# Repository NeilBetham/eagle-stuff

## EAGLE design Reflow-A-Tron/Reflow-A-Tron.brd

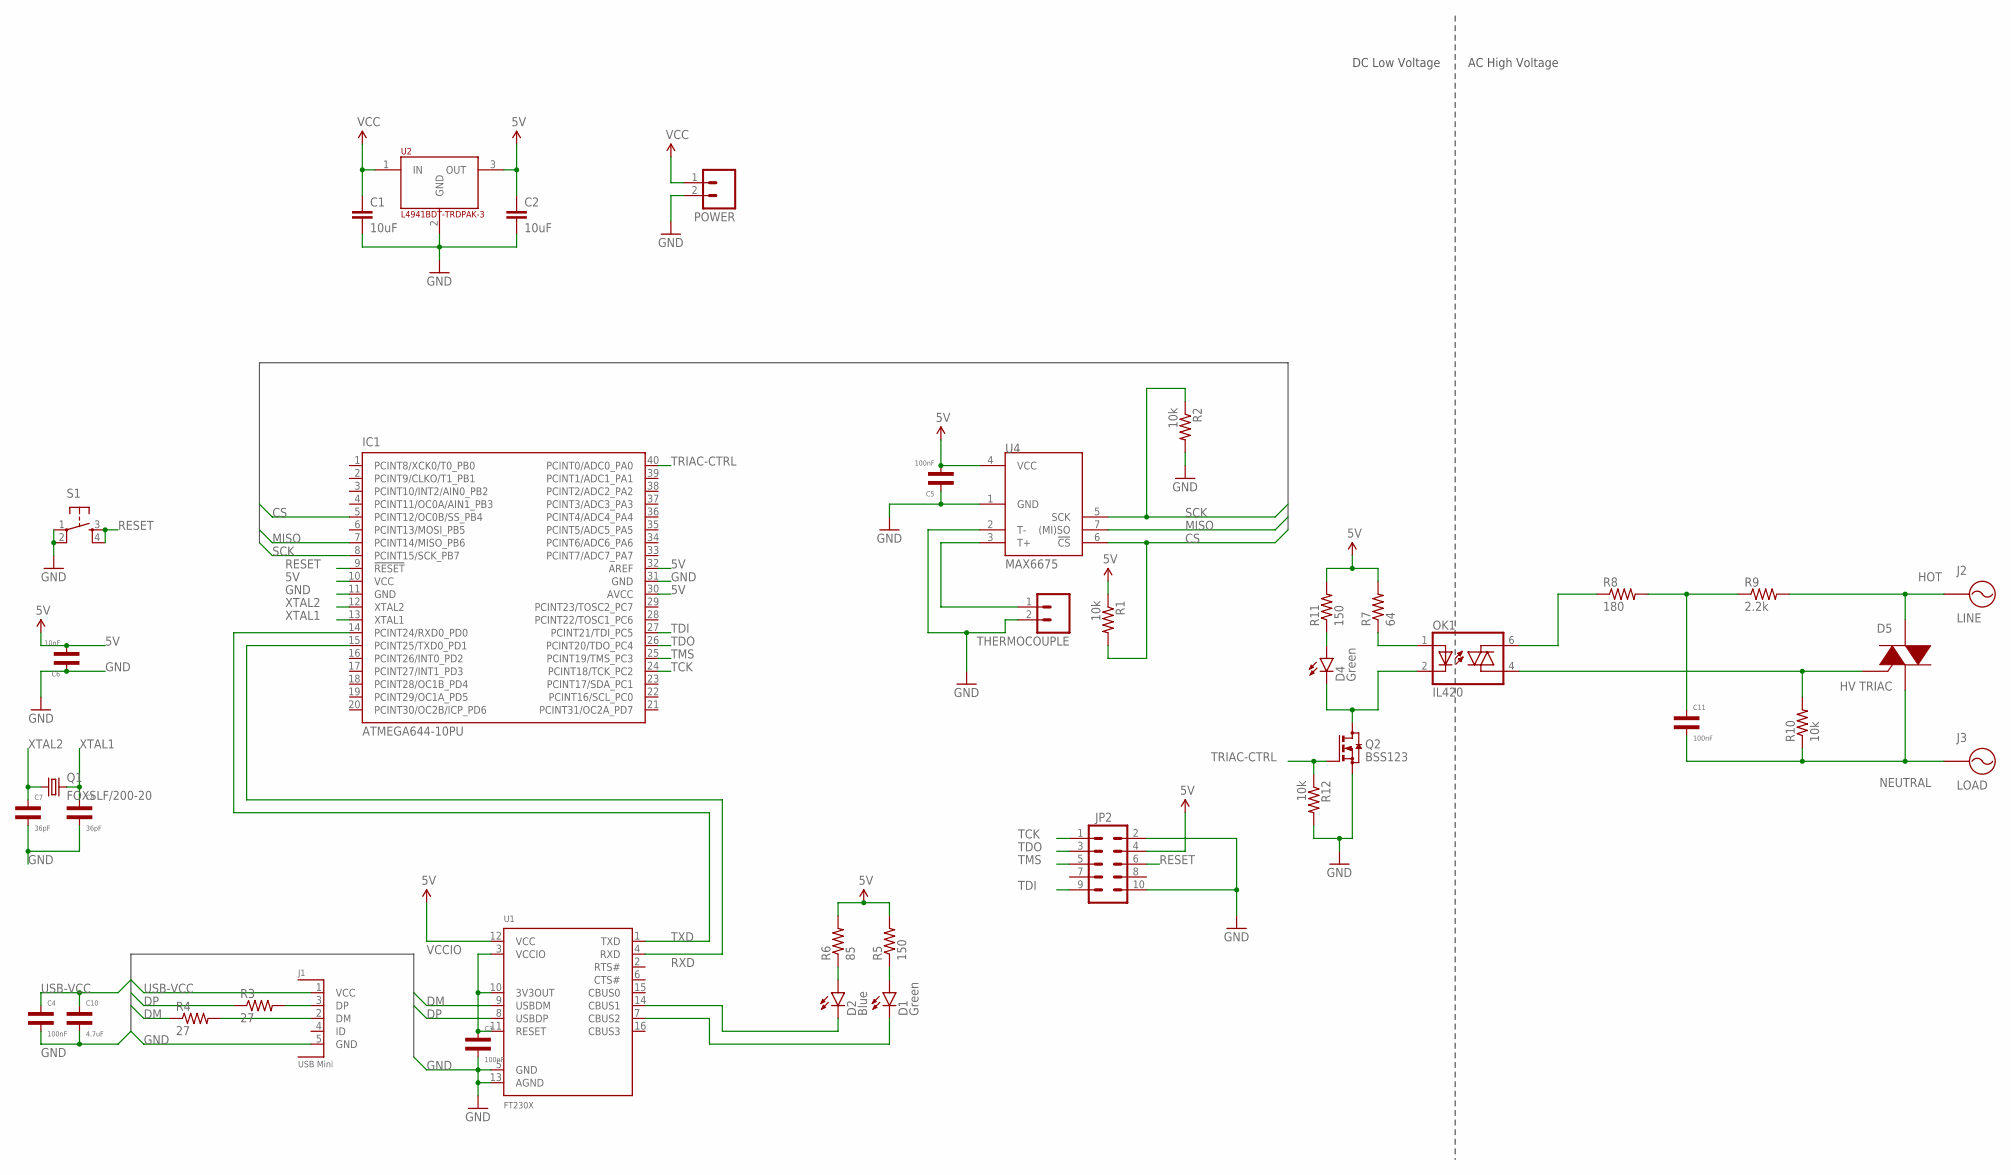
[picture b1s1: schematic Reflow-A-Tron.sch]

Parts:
C1, C2: 10uF; 1210
C3, C4, C5, C11: 100nF; 0805
C6: 10nF; 0805
C7, C8: 36pF; 0805
C10: 4.7uF; 0805
D1, D4: Green; LED-1206
D2: Blue; LED-1206
D5: HV TRIAC; D2PAK
IC1: ATMEGA644-10PU; DIL40
J1: USB Mini; XM7D-0512
J2: LINE; 8191
J3: LOAD; 8191
JP2: M05X2PTH; AVR_ICSP
OK1: IL420; DIL06
POWER: M025MM; SCREWTERMINAL-5MM-2
Q1: FOXSLF/200-20; HC49/S
Q2: BSS123; SOT23
R1, R2, R10, R12: 10k; R0805
R3, R4: 27; M0805
R5, R11: 150; R0805
R6: 85; R0805
R7: 64; R0805
R8: 180; R0805
R9: 2.2k; R0805
S1: TAC_SWITCHPTH; TACTILE-PTH
THERMOCOUPLE: M023.5MM; SCREWTERMINAL-3.5MM-2
U1: FT230X; SSOP-16
U2: L4941BDT-TRDPAK-3; DPAK
U4: MAX6675; SOIC8

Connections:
5V: C2.1, C5.1, C6.1, IC1.10 (VCC), IC1.30 (AVCC), IC1.32 (AREF), JP2.4, R1.1, R5.2, R6.2, R7.2, R11.2, U1.12 (VCC), U2.3 (OUT), U4.4 (VCC)
CS: IC1.5 (PCINT12/OC0B/SS_PB4), R1.2, U4.6 (!CS)
DM: R4.1, U1.9 (USBDM)
DP: R3.1, U1.8 (USBDP)
GND: C1.2, C2.2, C3.1, C4.1, C5.2, C6.2, C7.1, C8.1, C10.1, IC1.11 (GND), IC1.31 (GND), J1.5 (GND), JP2.2, JP2.10, POWER.2, Q2.2 (S), R2.2, R12.2, S1.1, S1.2, THERMOCOUPLE.2, U1.5 (GND), U1.13 (AGND), U2.2 (GND), U4.1 (GND), U4.2 (T-)
HOT: D5.4 (A2), J2.1, J2.2, J2.3, J2.4, R9.2
MISO: IC1.7 (PCINT14/MISO_PB6), U4.7 ((MI)SO)
unnamed: J1.2 (DM), R4.2
unnamed: J1.3 (DP), R3.2
unnamed: D1.A, R5.1
unnamed: D2.A, R6.1
unnamed: D2.C, U1.14 (CBUS1)
unnamed: D1.C, U1.7 (CBUS2)
unnamed: OK1.6 (A2), R8.1
unnamed: OK1.1 (A), R7.1
unnamed: D5.3 (G), OK1.4 (A1), R10.2
unnamed: C11.2, R8.2, R9.1
unnamed: D4.C, OK1.2 (C), Q2.3 (D)
unnamed: D4.A, R11.1
NEUTRAL: C11.1, D5.1 (A1), J3.1, J3.2, J3.3, J3.4, R10.1
RESET: IC1.9 (!RESET), JP2.6, S1.3, S1.4
RXD: IC1.15 (PCINT25/TXD0_PD1), U1.4 (RXD)
SCK: IC1.8 (PCINT15/SCK_PB7), R2.1, U4.5 (SCK)
T+: THERMOCOUPLE.1, U4.3 (T+)
TCK: IC1.24 (PCINT18/TCK_PC2), JP2.1
TDI: IC1.27 (PCINT21/TDI_PC5), JP2.9
TDO: IC1.26 (PCINT20/TDO_PC4), JP2.3
TMS: IC1.25 (PCINT19/TMS_PC3), JP2.5
TRIAC-CTRL: IC1.40 (PCINT0/ADC0_PA0), Q2.1 (G), R12.1
TXD: IC1.14 (PCINT24/RXD0_PD0), U1.1 (TXD)
USB-VCC: C4.2, C10.2, J1.1 (VCC)
VCC: C1.1, POWER.1, U2.1 (IN)
VCCIO: C3.2, U1.3 (VCCIO), U1.10 (3V3OUT), U1.11 (RESET)
XTAL1: C8.2, IC1.13 (XTAL1), Q1.2
XTAL2: C7.2, IC1.12 (XTAL2), Q1.1

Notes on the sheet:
DC Low Voltage
AC High Voltage

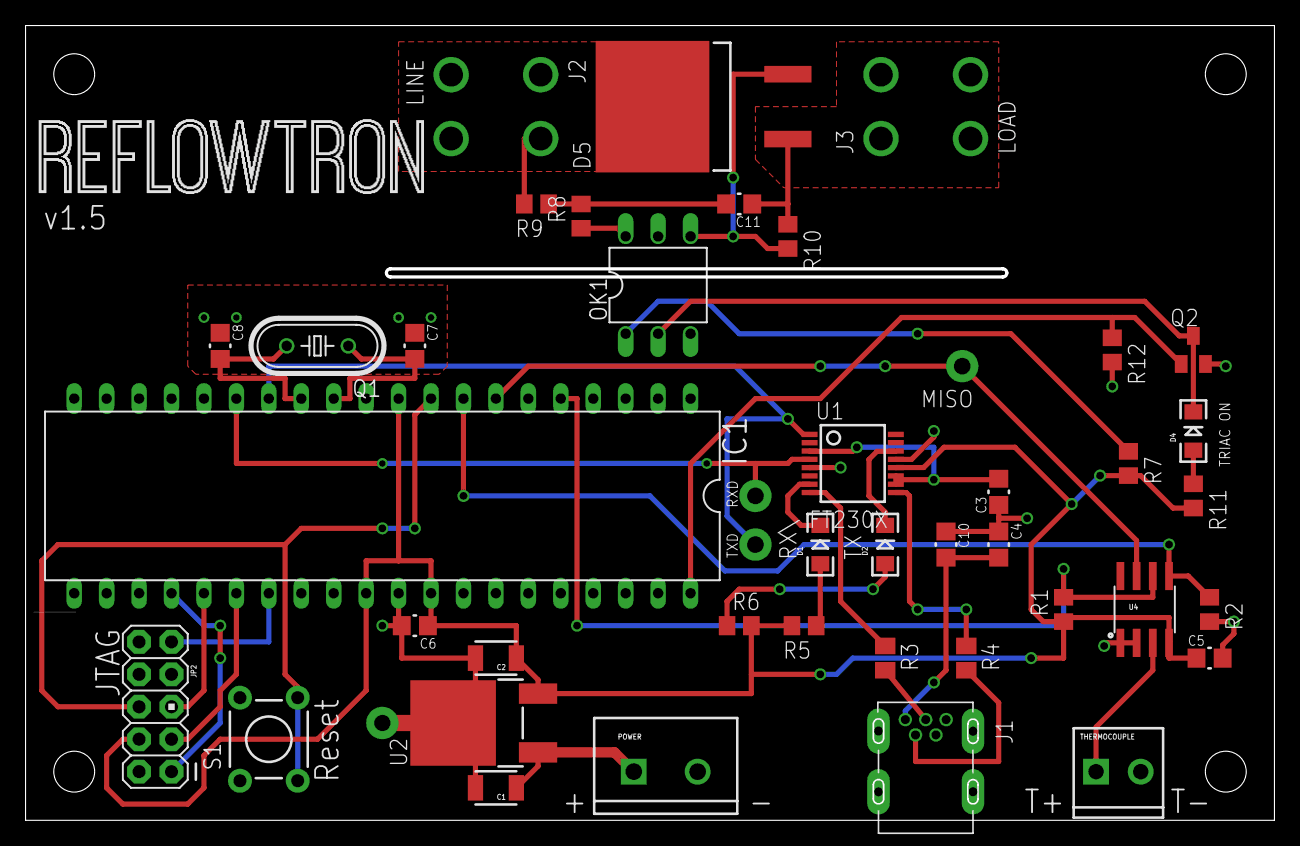
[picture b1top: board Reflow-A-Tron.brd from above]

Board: 2 copper layers, 97.8 x 62.2 mm, 40 parts (0 on the bottom side), 35 nets.

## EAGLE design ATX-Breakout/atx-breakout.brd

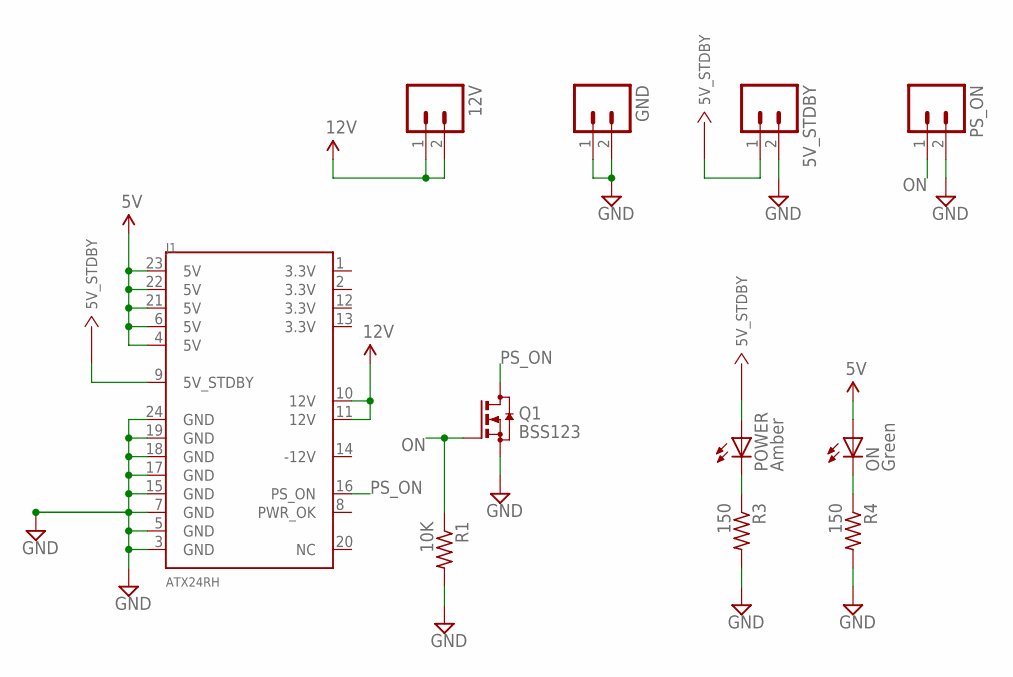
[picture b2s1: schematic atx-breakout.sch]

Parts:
5V_STDBY, 12V: M025MM; SCREWTERMINAL-5MM-2
GND: M025MM; SCREWTERMINAL-5MM-2
J1: ATX24RH; ATX24_RIGHT_ANGLE
ON: Green; CHIP-LED0805
POWER: Amber; CHIP-LED0805
PS_ON: M025MM; SCREWTERMINAL-5MM-2
Q1: BSS123; SOT23
R1: 10K; R0805
R3, R4: 150; R0805

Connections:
5V: J1.4 (5V), J1.6 (5V), J1.21 (5V), J1.22 (5V), J1.23 (5V), ON.A
5V_STDBY: 5V_STDBY.1, J1.9 (5V_STDBY), POWER.A
12V: 12V.1, 12V.2, J1.10 (12V), J1.11 (12V)
GND: 5V_STDBY.2, GND.1, GND.2, J1.3 (GND), J1.5 (GND), J1.7 (GND), J1.15 (GND), J1.17 (GND), J1.18 (GND), J1.19 (GND), J1.24 (GND), PS_ON.2, Q1.2 (S), R1.2, R3.2, R4.2
unnamed: POWER.C, R3.1
unnamed: ON.C, R4.1
ON: PS_ON.1, Q1.1 (G), R1.1
PS_ON: J1.16 (PS_ON), Q1.3 (D)

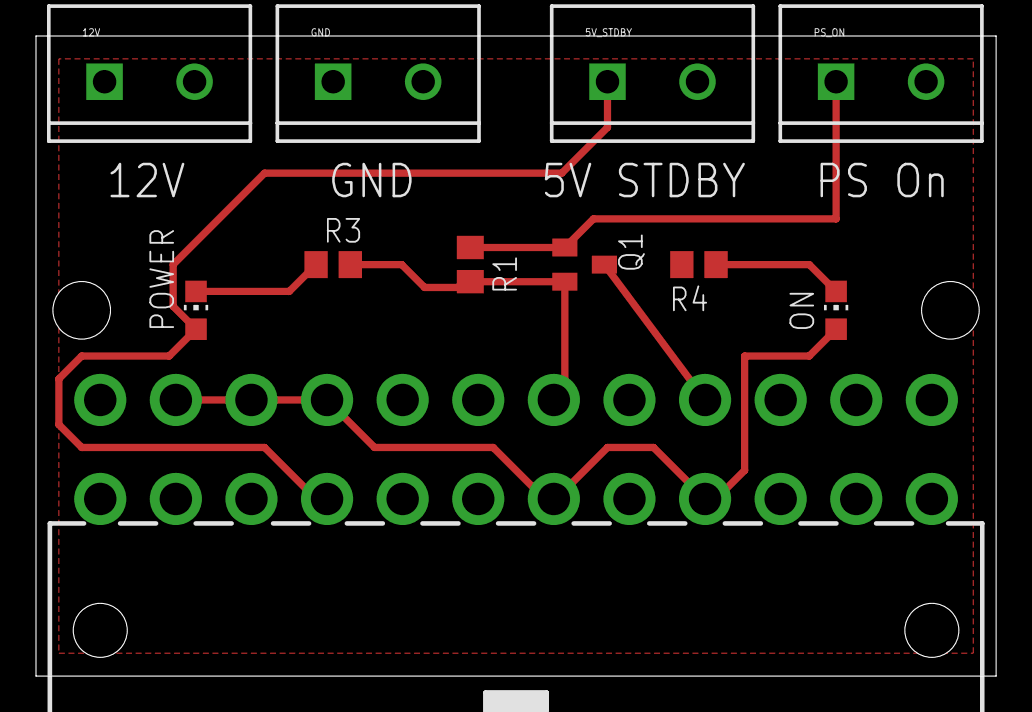
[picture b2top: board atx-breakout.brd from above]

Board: 2 copper layers, 53.3 x 35.6 mm, 11 parts (0 on the bottom side), 8 nets.

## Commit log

2015-07-24 Add ATX breakout board for mendel reprap
2015-11-16 reflow controller work
2015-11-21 more reflow controller work
2015-11-22 JTAG programming
2015-11-22 triac connected
2015-11-22 layout complete
2015-11-22 Name
2015-11-22 version number
2015-11-22 Only keep relevant data sheets
2015-11-22 Tent vias
2015-11-22 tName not bName
2015-11-22 lower res logo
2015-11-22 more bitmap bs
2015-12-11 Fix shit
2016-10-03 Move around datasheets, add todo list.
2016-10-10 More fixes
2016-10-24 Add custom lib, still needs more work.
2016-12-19 Next rev with more bug fixes
2017-08-02 Hardware Working for reflow a tron

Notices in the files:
parts and their libraries:
SparkFun-Connectors: Licensing: Creative Commons ShareAlike 4.0 International - https://creativecommons.org/licenses/by-sa/4.0
